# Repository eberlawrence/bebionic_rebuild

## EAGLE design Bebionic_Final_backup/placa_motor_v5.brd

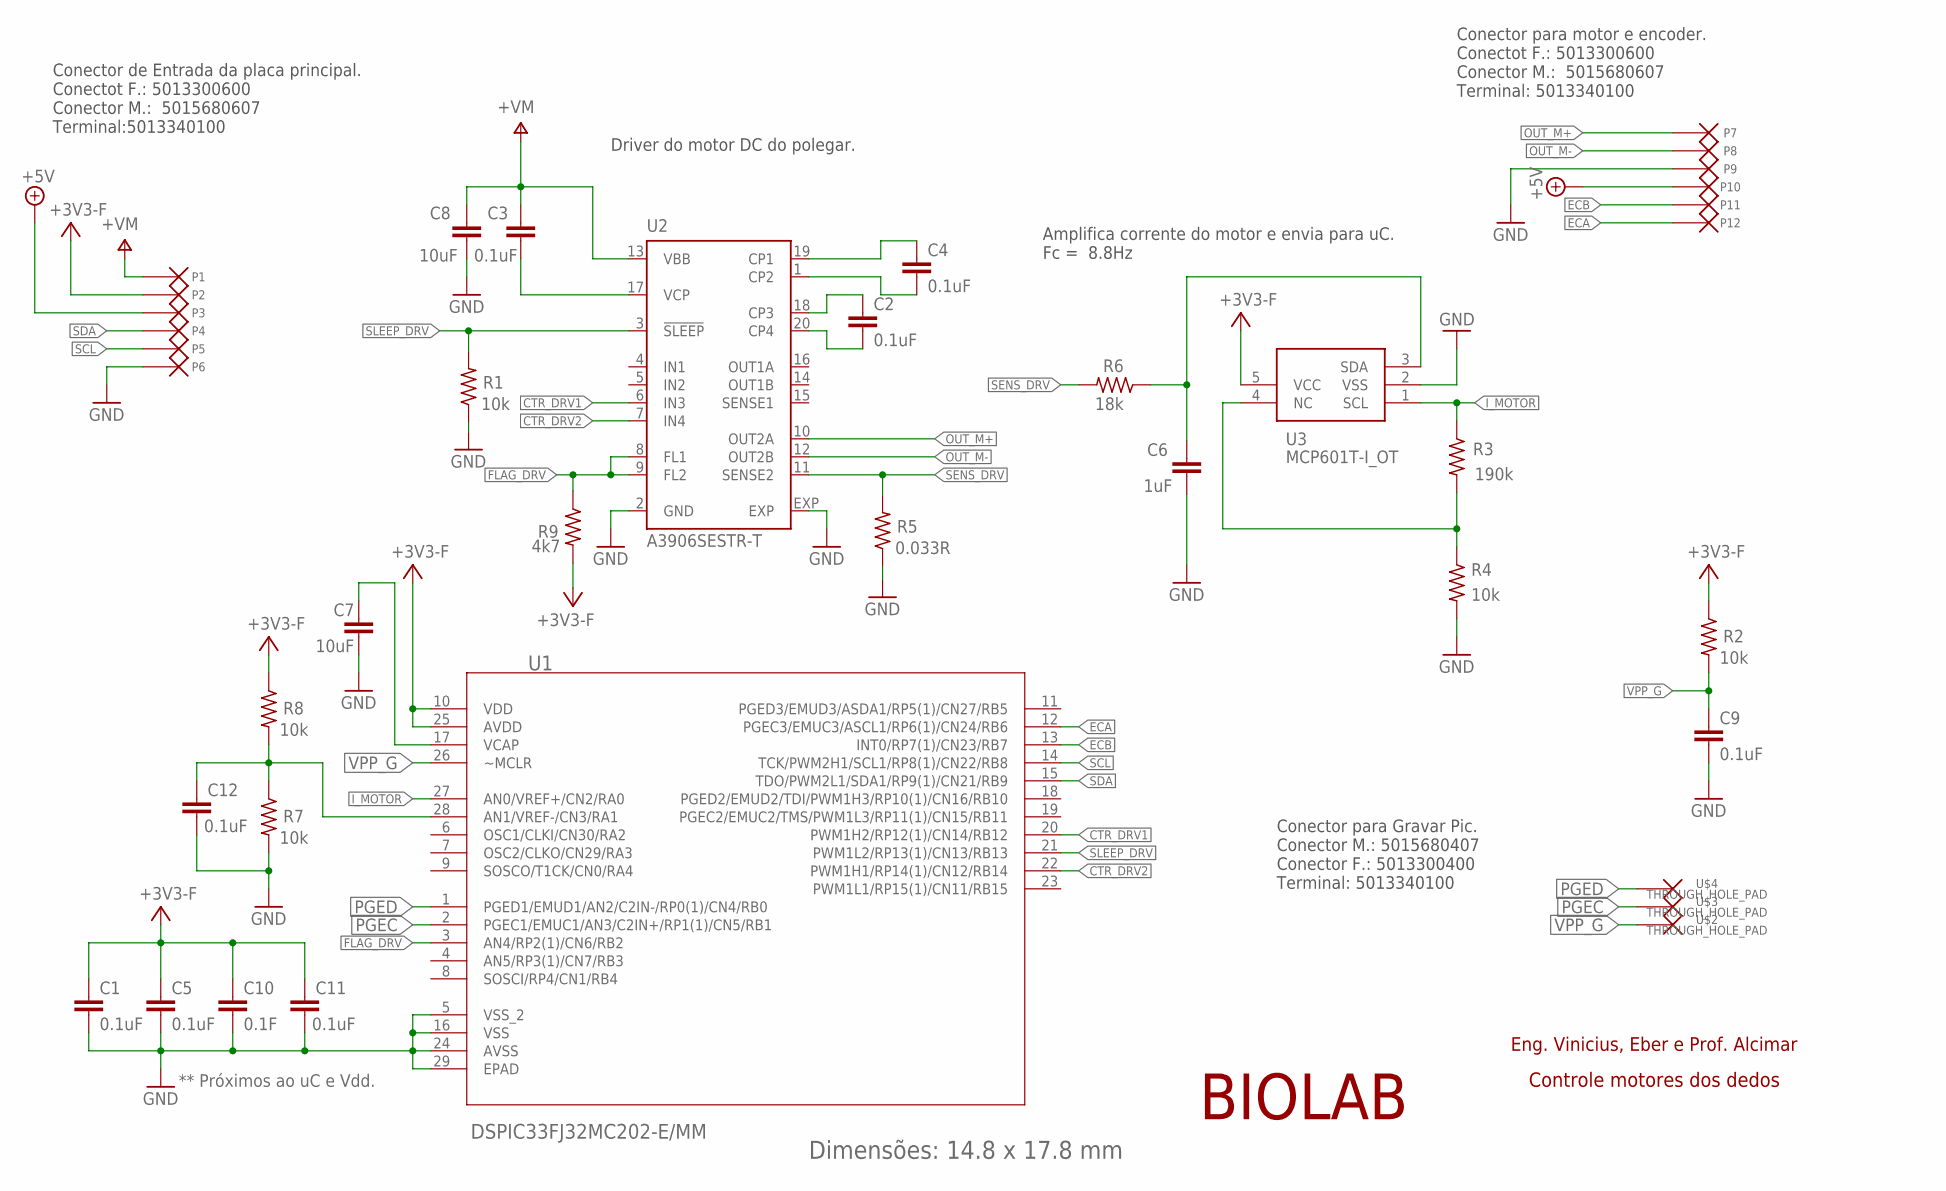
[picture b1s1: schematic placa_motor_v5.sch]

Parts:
C1, C2, C3, C4, C5, C9, C11, C12: 0.1uF; C0402K
C6: 1uF; C0402K
C7, C8: 10uF; C0805K
C10: 0.1F; C0402K
P1, P2, P3, P4, P5, P6, P7, P8, P9, P10, P11, P12: THROUGH_HOLE_PAD
R1, R2, R4, R7, R8: 10k; R0402
R3: 190k; R0402
R5: 0.033R; R0805
R6: 18k; R0402
R9: 4k7; R0402
U1: DSPIC33FJ32MC202-E/MM; QFN65P600X600X100-29N
U2: A3906SESTR-T; QFN20
U3: MCP601T-I_OT; SOT95P270X145-5N
U$2, U$3, U$4: THROUGH_HOLE_PAD

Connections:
+3V3: C1.1, C5.1, C10.1, C11.1, P2.P$1, R2.1, R8.1, R9.2, U1.10 (VDD), U1.25 (AVDD), U3.5 (VCC)
+5V: P3.P$1, P10.P$1
AUX: C12.1, R7.1, R8.2, U1.28 (AN1/VREF-/CN3/RA1)
CTR_DRV1: U1.20 (PWM1H2/RP12(1)/CN14/RB12), U2.6 (IN3)
CTR_DRV2: U1.22 (PWM1H1/RP14(1)/CN12/RB14), U2.7 (IN4)
ECA: P12.P$1, U1.12 (PGEC3/EMUC3/ASCL1/RP6(1)/CN24/RB6)
ECB: P11.P$1, U1.13 (INT0/RP7(1)/CN23/RB7)
FLAG_DRV: R9.1, U1.3 (AN4/RP2(1)/CN6/RB2), U2.8 (FL1), U2.9 (FL2)
GND: C1.2, C5.2, C6.2, C7.2, C8.1, C9.2, C10.2, C11.2, C12.2, P6.P$1, P9.P$1, R1.1, R4.2, R5.1, R7.2, U1.5 (VSS_2), U1.16 (VSS), U1.24 (AVSS), U1.29 (EPAD), U2.2 (GND), U2.EXP, U3.2 (VSS)
I_MOTOR: R3.1, U1.27 (AN0/VREF+/CN2/RA0), U3.1 (SCL)
N1: C7.1, U1.17 (VCAP)
N2: R3.2, R4.1, U3.4 (NC)
N3: C6.1, R6.1, U3.3 (SDA)
N4: C4.1, U2.19 (CP1)
N5: C4.2, U2.1 (CP2)
N6: C2.1, U2.18 (CP3)
N7: C2.2, U2.20 (CP4)
N8: C3.2, U2.17 (VCP)
OUT_M+: P7.P$1, U2.10 (OUT2A)
OUT_M-: P8.P$1, U2.12 (OUT2B)
PGEC: U1.2 (PGEC1/EMUC1/AN3/C2IN+/RP1(1)/CN5/RB1), U$3.P$1
PGED: U1.1 (PGED1/EMUD1/AN2/C2IN-/RP0(1)/CN4/RB0), U$4.P$1
SCL: P5.P$1, U1.14 (TCK/PWM2H1/SCL1/RP8(1)/CN22/RB8)
SDA: P4.P$1, U1.15 (TDO/PWM2L1/SDA1/RP9(1)/CN21/RB9)
SENS_DRV: R5.2, R6.2, U2.11 (SENSE2)
SLEEP_DRV: R1.2, U1.21 (PWM1L2/RP13(1)/CN13/RB13), U2.3 (!SLEEP)
V+: C3.1, C8.2, P1.P$1, U2.13 (VBB)
VPP_G: C9.1, R2.2, U1.26 (~MCLR), U$2.P$1

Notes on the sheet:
Dimensões: 14.8 x 17.8 mm
** Próximos ao uC e Vdd.
Conector para motor e encoder. Conectot F.: 5013300600 Conector M.: 5015680607 Terminal: 5013340100
Conector de Entrada da placa principal. Conectot F.: 5013300600 Conector M.: 5015680607 Terminal:5013340100
BIOLAB
Eng. Vinicius, Eber e Prof. Alcimar
Driver do motor DC do polegar.
Amplifica corrente do motor e envia para uC. Fc = 8.8Hz
Controle motores dos dedos
Conector para Gravar Pic. Conector M.: 5015680407 Conector F.: 5013300400 Terminal: 5013340100

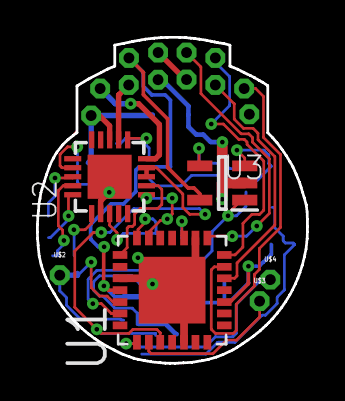
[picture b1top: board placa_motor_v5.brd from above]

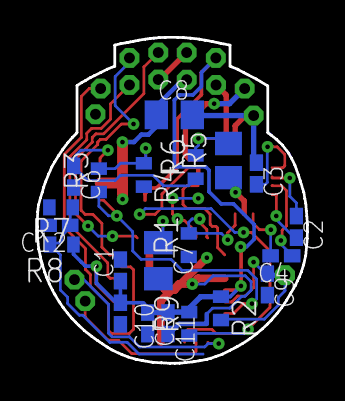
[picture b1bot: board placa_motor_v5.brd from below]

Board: 2 copper layers, 15.0 x 18.1 mm, 39 parts (22 on the bottom side), 28 nets.

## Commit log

2020-04-09 Starting
2020-04-09 Updating
2020-04-13 Updating README
2020-04-28 Updating[B
